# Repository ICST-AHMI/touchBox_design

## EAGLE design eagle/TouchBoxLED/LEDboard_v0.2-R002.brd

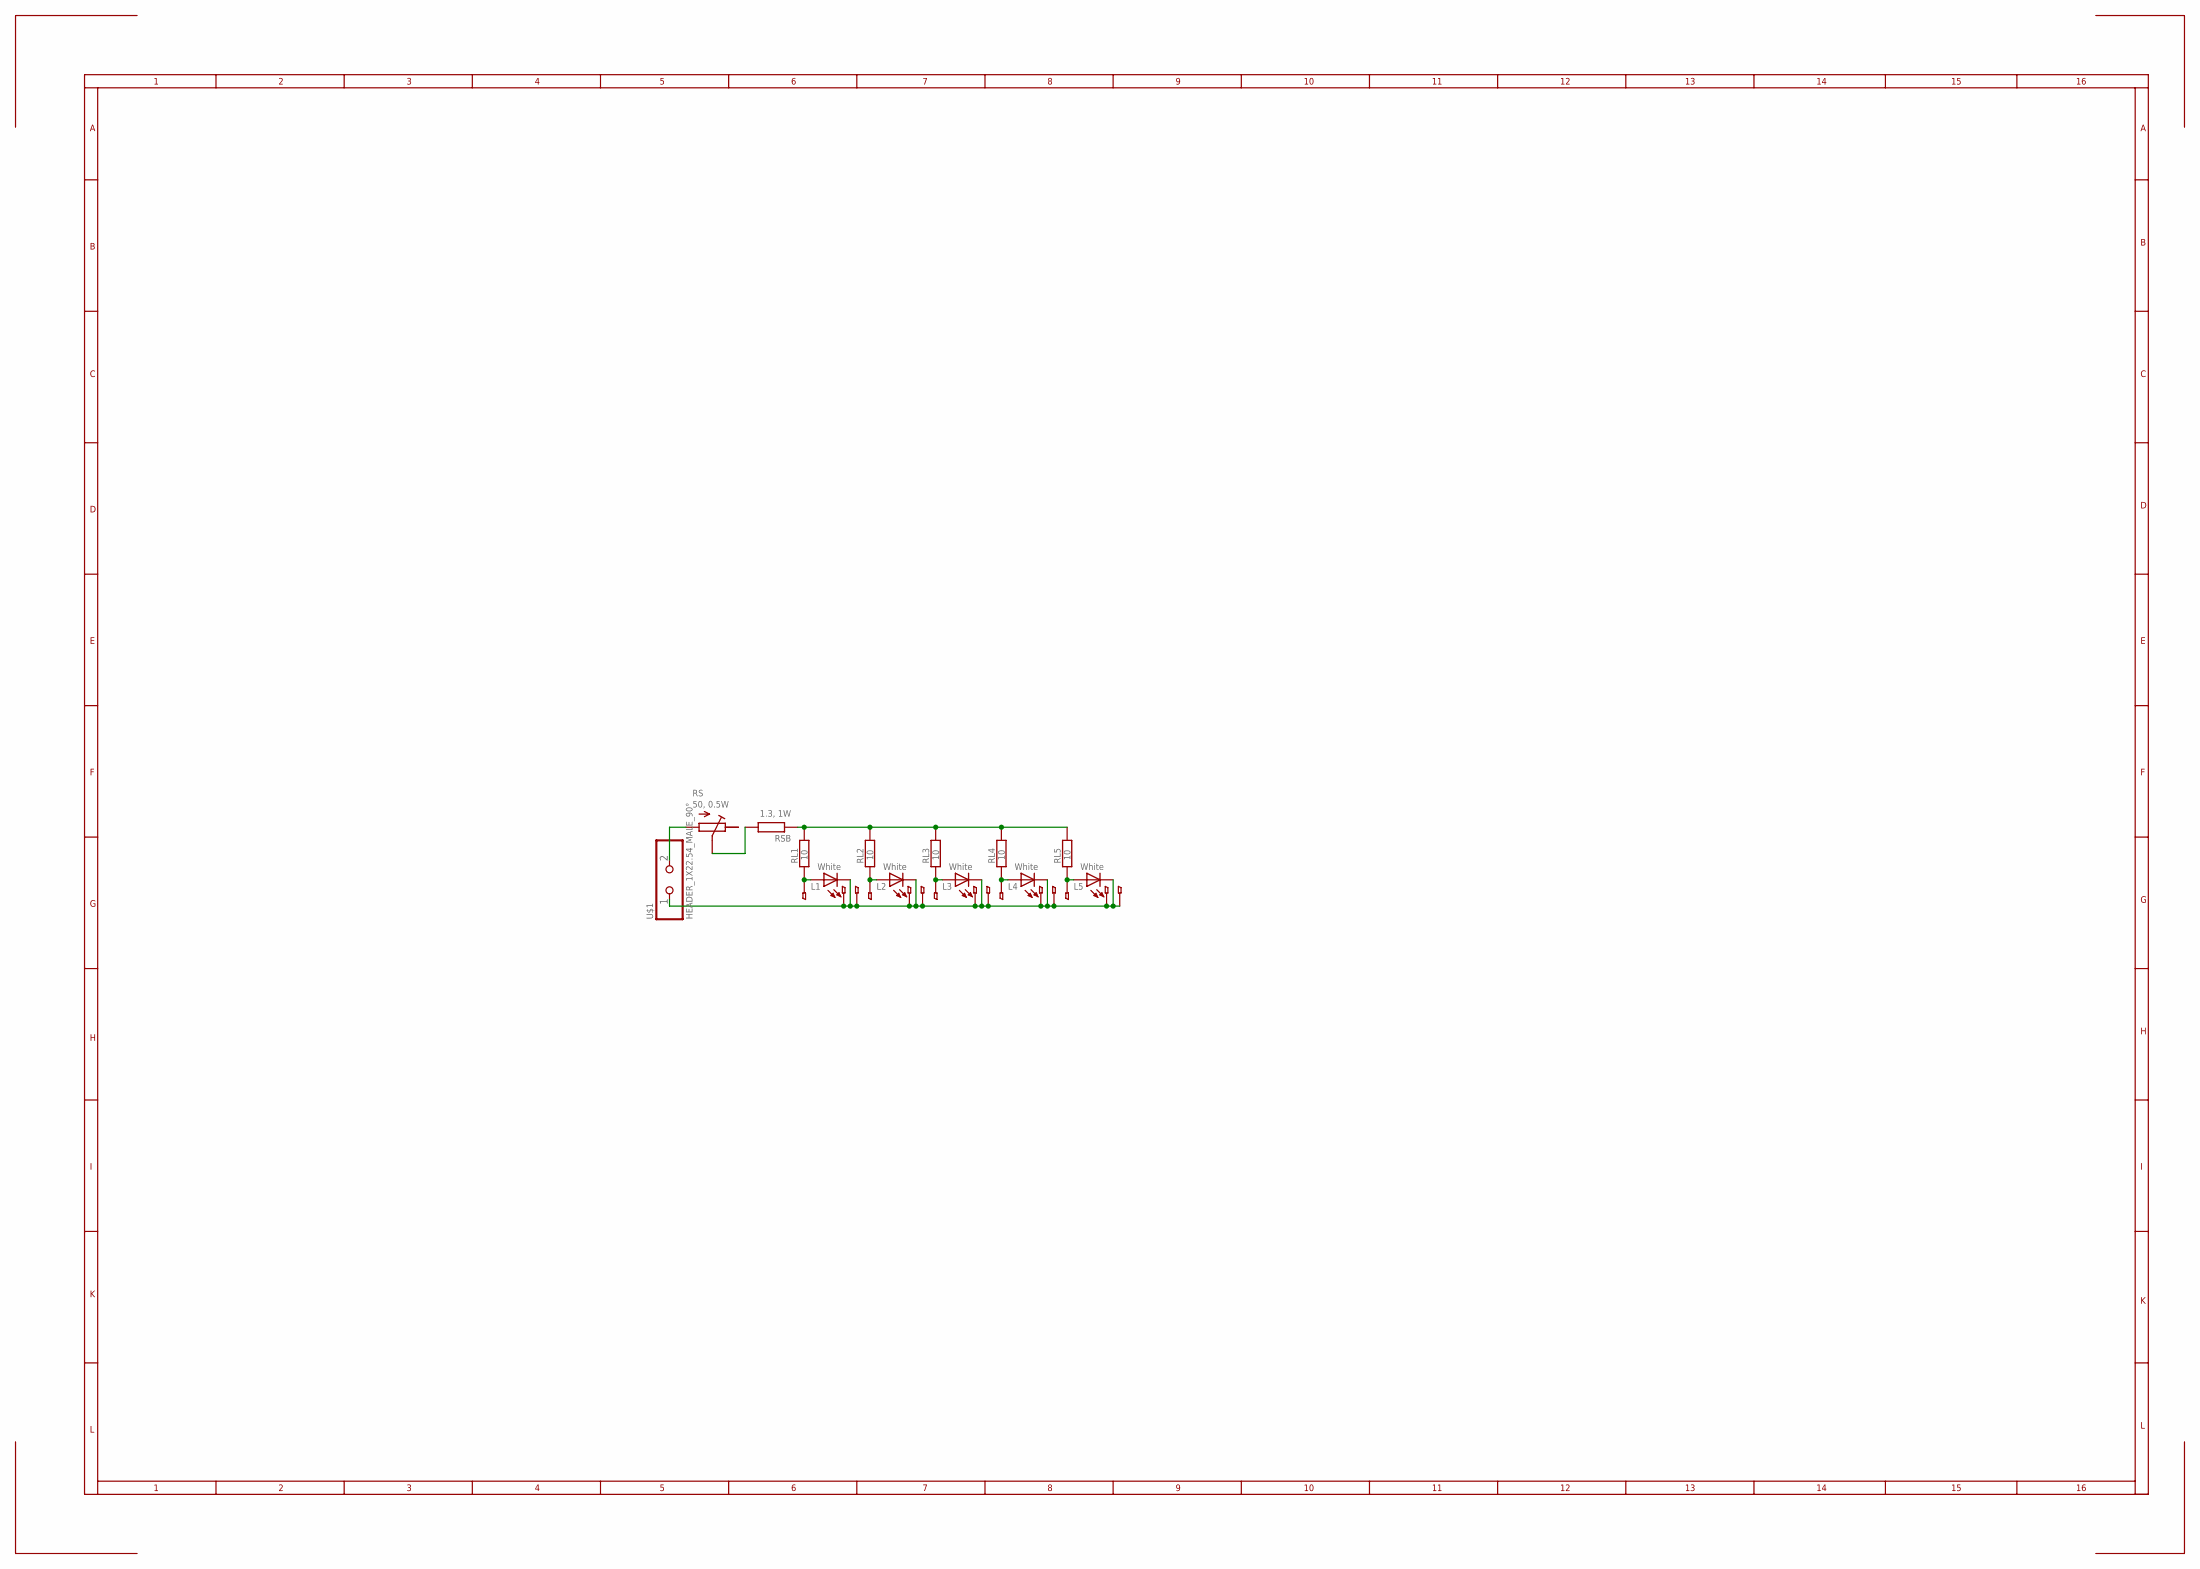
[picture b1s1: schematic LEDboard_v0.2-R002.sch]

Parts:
L1, L2, L3, L4, L5: White; LED_LM561B
RL1, RL2, RL3, RL4, RL5: 10; R0805
RS: 50, 0.5W; RTRIM3290H
RSB: 1.3, 1W; 0207/10
U$1: HEADER_1X22.54_MALE_90°; 1X02_2.54_90

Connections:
0V: L1.C1 (C), L1.C2 (1), L1.C3 (1), L2.C1 (C), L2.C2 (1), L2.C3 (1), L3.C1 (C), L3.C2 (1), L3.C3 (1), L4.C1 (C), L4.C2 (1), L4.C3 (1), L5.C1 (C), L5.C2 (1), L5.C3 (1), U$1.1
unnamed: RS.2 (S), RSB.2
unnamed: RL1.2, RL2.2, RL3.2, RL4.2, RL5.2, RSB.1
unnamed: L1.A1 (A), L1.A2 (1), RL1.1
unnamed: L2.A1 (A), L2.A2 (1), RL2.1
unnamed: L5.A1 (A), L5.A2 (1), RL5.1
unnamed: L4.A1 (A), L4.A2 (1), RL4.1
unnamed: L3.A1 (A), L3.A2 (1), RL3.1
unnamed: RS.1 (E), U$1.2

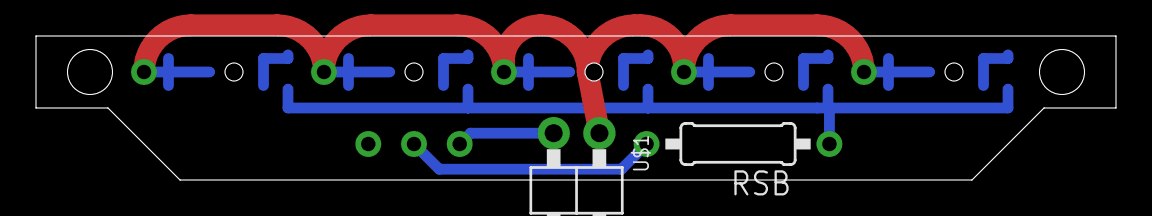
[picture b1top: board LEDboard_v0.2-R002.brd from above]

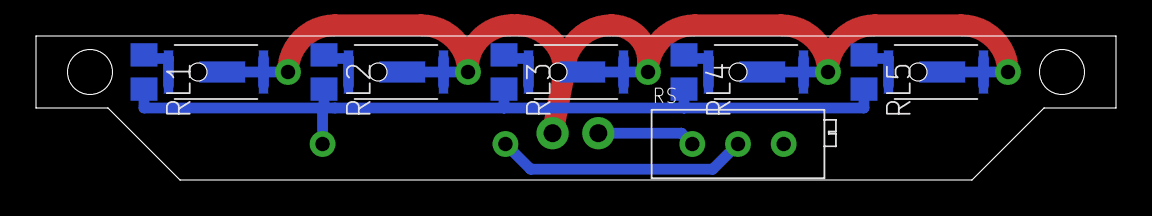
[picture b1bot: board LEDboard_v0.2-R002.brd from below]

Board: 2 copper layers, 60.0 x 8.0 mm, 13 parts (11 on the bottom side), 9 nets.

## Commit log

2015-09-14 added blender files
2015-09-30 added resistor values to documents
2015-10-06 added some details to the description of devices
